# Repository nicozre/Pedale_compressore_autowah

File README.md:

# Pedale per chitarra: compressore a OTA + auto-wah

Progetto open source di un pedale per chitarra analogico che combina in un'unica scheda un **compressore** (OTA con *current stealing*) e un effetto **auto-wah** (filtro a due poli OTA-C con risonanza). Tutti i componenti sono a foro passante (THT), così da poter essere saldati a mano.

Il progetto nasce come tesi di laurea (Università degli studi di Trento, Dipartimento di ingegneria industriale: Robotica e Meccatronica, a.a. 2025/2026, autore Nicolò Ozretić, relatore Lucio Pancheri).

> ## ⚠️ Stato del progetto: NON ancora concluso
>
> - Il progetto è alla **fase di progettazione e simulazione**: il pedale **non è stato ancora costruito né misurato**.
> - I risultati riportati (guadagno, soglia, consumi, distorsione) vengono da simulazioni LTspice, non da misure.
> - Le schede **non sono state ordinate né verificate**: se le ordini, lo fai a tuo rischio.
> - È nota almeno una modifica da introdurre al prototipo: un **resistore di shunt (circa 680 Ω)** tra l'ingresso invertente dell'OTA del VCA e V<sub>bias</sub>, che realizza nel circuito reale l'attenuazione d'ingresso assunta nelle simulazioni. Non è ancora nello schema KiCad (vedi la tesi, Capitolo 5 e Conclusioni).
> - Questo repository verrà aggiornato man mano che il lavoro prosegue. Controlla la sezione *Cronologia* per le novità.

## Caratteristiche (da simulazione)

| | |
|---|---|
| Alimentazione | solo alimentatore da muro a 9 V (nessuna batteria) |
| Consumo | 19–23 mA senza LED, 26–30 mA con LED (233–271 mW) |
| Compressore | guadagno ≈ 10 dB sotto soglia, soglia ≈ 250 mV, rapporto ≈ 2,6:1, attacco ≈ 4 ms, rilascio ≈ 200 ms |
| Auto-wah | picco di risonanza ≈ 13 dB (Q ≈ 4,5), frequenza di picco da ≈ 235 Hz a ≈ 2,6 kHz, comandata dall'inviluppo |
| Componenti attivi | 2 × LM13700, 2 × TL074, TLE2426 (massa virtuale 4,5 V) |
| Controlli | SUSTAIN, DECAY, SENS, MASTER, trimmer di livello |
| Footswitch | 3PDT (serie FS5700) |

## Contenuto del repository

```
hardware/   progetto KiCad (schema, circuito stampato, librerie)
produzione/ file Gerber, distinta componenti (BOM) e posizioni, per ordinare la scheda
simulazioni/ file LTspice e script
tesi/       sorgenti LaTeX e PDF della tesi
docs/       tutorial (acquisto, montaggio, prove)
```

*(La struttura potrà cambiare: i file si aggiungeranno man mano.)*

## Tutorial: ordinare e costruire il pedale

> Il tutorial completo sarà pubblicato qui in `docs/` quando il progetto sarà verificato su un prototipo. Questa è la traccia di ciò che conterrà.

1. **Strumenti necessari**: saldatore a stagno, stagno, tronchesine, multimetro, cacciaviti, alimentatore da muro a 9 V (centro negativo, come la maggior parte dei pedali), cavi jack.
2. **Ordinare il circuito stampato**: caricare i file Gerber della cartella `produzione/` su un servizio di produzione di PCB (JLCPCB, PCBWay o simili) e scegliere le opzioni indicate nel tutorial (spessore, finitura, numero di strati).
3. **Ordinare i componenti**: dalla distinta componenti (BOM) in `produzione/`, presso un distributore di componenti elettronici (Mouser, Farnell, Digi-Key, RS o simili). Il tutorial indicherà le alternative equivalenti per i componenti più difficili da reperire.
4. **Montaggio**: ordine di saldatura consigliato (resistori, diodi, zoccoli per i circuiti integrati, condensatori, transistor, componenti ingombranti, potenziometri, connettori, footswitch), con attenzione alla polarità dei condensatori elettrolitici, dei diodi e dei circuiti integrati.
5. **Prima accensione e prove**: controllo della tensione di alimentazione e di V<sub>bias</sub> (4,5 V) prima di inserire i circuiti integrati, verifica dei consumi, prova con una chitarra e regolazione del trimmer.
6. **Contenitore**: forature, montaggio dei controlli e del footswitch.

### Preventivo indicativo

Un preventivo del costo di scheda e componenti **non è ancora disponibile**: verrà aggiunto qui quando saranno disponibili i prezzi di un fornitore di PCB e di un distributore di componenti (con la data di consultazione).

## Sorgenti della tesi

La cartella `tesi/` contiene il progetto LaTeX (compilabile con `pdflatex`, ad esempio su Overleaf) e il PDF.

## Licenza

*Da definire.* Per un progetto di hardware aperto si prevede una licenza CERN-OHL per i file di progetto e una licenza Creative Commons (CC BY) per la documentazione. Fino a quando non sarà aggiunto un file `LICENSE`, valgono i diritti d'autore dell'autore.

## Cronologia

- **novembre 2026**: prima pubblicazione del repository (progetto in fase di progettazione e simulazione).

## Contatti e contributi

Per segnalazioni, errori o miglioramenti apri una *Issue* in questo repository. I contributi sono benvenuti, in particolare le misure sul prototipo, se lo costruisci.

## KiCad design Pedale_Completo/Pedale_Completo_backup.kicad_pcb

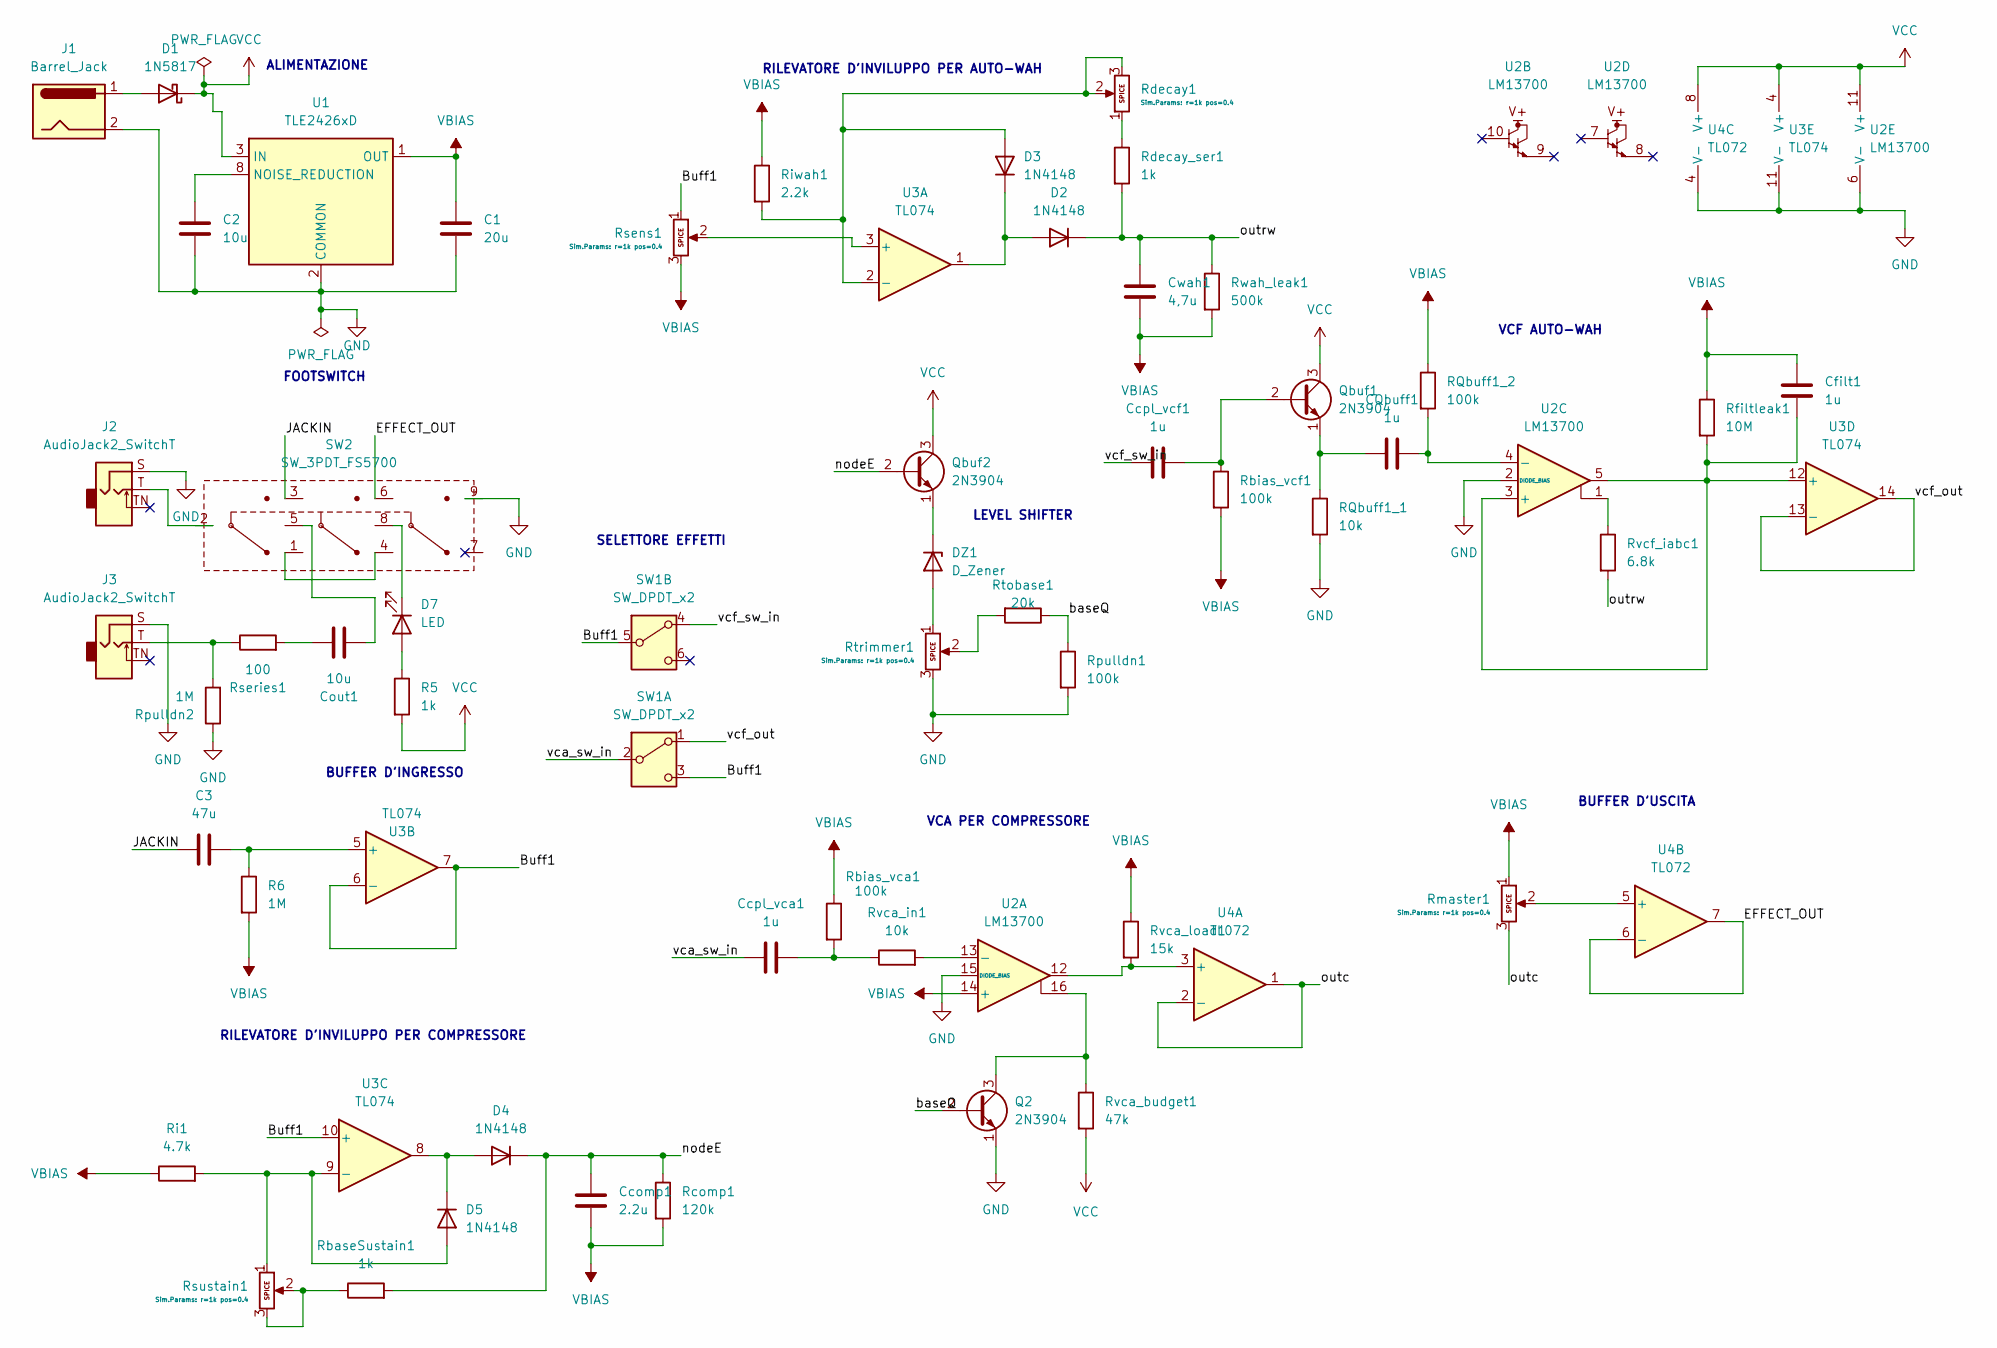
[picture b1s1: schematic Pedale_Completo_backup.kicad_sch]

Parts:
C1: 20u; CP_Radial_D5.0mm_P2.00mm
C2: 10u; CP_Radial_D5.0mm_P2.00mm
C3: 47u; CP_Radial_D6.3mm_P2.50mm
CQbuff1: 1u; CP_Radial_D5.0mm_P2.00mm
Ccomp1: 2.2u; CP_Radial_D5.0mm_P2.00mm
Ccpl_vca1: 1u; CP_Radial_D5.0mm_P2.00mm
Ccpl_vcf1: 1u; CP_Radial_D5.0mm_P2.00mm
Cfilt1: 1u; C_Disc_D5.0mm_W2.5mm_P5.00mm
Cout1: 10u; CP_Radial_D5.0mm_P2.00mm
Cwah1: 4,7u; CP_Radial_D5.0mm_P2.00mm
D1: 1N5817; D_DO-41_SOD81_P10.16mm_Horizontal
D2, D3, D4, D5: 1N4148; D_DO-35_SOD27_P7.62mm_Horizontal
D7: LED; LED_D5.0mm
DZ1: D_Zener; D_DO-35_SOD27_P7.62mm_Horizontal
J1: Barrel_Jack; BarrelJack_CUI_PJ-102AH_Horizontal
J2, J3: AudioJack2_SwitchT; Jack_Mono_SwitchedT_PCB_ACJM
Q2: 2N3904; TO-92_Inline
Qbuf1, Qbuf2: 2N3904; TO-92_Inline
R5: 1k; R_Axial_DIN0207_L6.3mm_D2.5mm_P10.16mm_Horizontal
R6: 1M; R_Axial_DIN0207_L6.3mm_D2.5mm_P10.16mm_Horizontal
RQbuff1_1: 10k; R_Axial_DIN0207_L6.3mm_D2.5mm_P10.16mm_Horizontal
RQbuff1_2: 100k; R_Axial_DIN0207_L6.3mm_D2.5mm_P10.16mm_Horizontal
RbaseSustain1: 1k; R_Axial_DIN0207_L6.3mm_D2.5mm_P10.16mm_Horizontal
Rbias_vca1: 100k; R_Axial_DIN0207_L6.3mm_D2.5mm_P10.16mm_Horizontal
Rbias_vcf1: 100k; R_Axial_DIN0207_L6.3mm_D2.5mm_P10.16mm_Horizontal
Rcomp1: 120k; R_Axial_DIN0207_L6.3mm_D2.5mm_P10.16mm_Horizontal
Rdecay1: Potentiometer; Potentiometer_Alps_RK09K_Single_Vertical
Rdecay_ser1: 1k; R_Axial_DIN0207_L6.3mm_D2.5mm_P10.16mm_Horizontal
Rfiltleak1: 10M; R_Axial_DIN0207_L6.3mm_D2.5mm_P10.16mm_Horizontal
Ri1: 4.7k; R_Axial_DIN0207_L6.3mm_D2.5mm_P10.16mm_Horizontal
Riwah1: 2.2k; R_Axial_DIN0207_L6.3mm_D2.5mm_P10.16mm_Horizontal
Rmaster1: Potentiometer; Potentiometer_Alps_RK09K_Single_Vertical
Rpulldn1: 100k; R_Axial_DIN0207_L6.3mm_D2.5mm_P10.16mm_Horizontal
Rpulldn2: 1M; R_Axial_DIN0207_L6.3mm_D2.5mm_P10.16mm_Horizontal
Rsens1: Potentiometer; Potentiometer_Alps_RK09K_Single_Vertical
Rseries1: 100; R_Axial_DIN0207_L6.3mm_D2.5mm_P10.16mm_Horizontal
Rsustain1: Potentiometer; Potentiometer_Alps_RK09K_Single_Vertical
Rtobase1: 20k; R_Axial_DIN0207_L6.3mm_D2.5mm_P10.16mm_Horizontal
Rtrimmer1: Potentiometer; Potentiometer_Bourns_3296W_Vertical
Rvca_budget1: 47k; R_Axial_DIN0207_L6.3mm_D2.5mm_P10.16mm_Horizontal
Rvca_in1: 10k; R_Axial_DIN0207_L6.3mm_D2.5mm_P10.16mm_Horizontal
Rvca_load1: 15k; R_Axial_DIN0207_L6.3mm_D2.5mm_P10.16mm_Horizontal
Rvcf_iabc1: 6.8k; R_Axial_DIN0207_L6.3mm_D2.5mm_P10.16mm_Horizontal
Rwah_leak1: 500k; R_Axial_DIN0207_L6.3mm_D2.5mm_P10.16mm_Horizontal
SW1: SW_DPDT_x2; SW_NKK_GW12LJP
SW2: SW_3PDT_FS5700
U1: TLE2426xD; DIP-8_W7.62mm
U2: LM13700; DIP-16_W7.62mm
U3: TL074; DIP-14_W7.62mm
U4: TL072; DIP-8_W7.62mm

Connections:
/Buff1: Rsens1.1, SW1.3 (C), SW1.5 (B), U3.6 (-), U3.7, U3.10 (+)
/EFFECT_OUT: SW2.6, U4.6 (-), U4.7
/JACKIN: C3.2, SW2.3
/baseQ: Q2.2 (B), Rpulldn1.1, Rtobase1.1
/nodeE: Ccomp1.1, D4.1 (K), Qbuf2.2 (B), RbaseSustain1.2, Rcomp1.1
/outc: Rmaster1.3, U4.1, U4.2 (-)
/outrw: Cwah1.1, D2.1 (K), Rdecay_ser1.2, Rvcf_iabc1.2, Rwah_leak1.1
/vca_sw_in: Ccpl_vca1.1, SW1.2 (B)
/vcf_out: SW1.1 (A), U3.13 (-), U3.14
/vcf_sw_in: Ccpl_vcf1.1, SW1.4 (A)
GND: C1.2, C2.2, J1.2, J2.S, J3.S, Q2.1 (E), RQbuff1_1.2, Rpulldn1.2, Rpulldn2.1, Rtrimmer1.3, SW2.9, U1.2 (COMMON), U2.2 (DIODE_BIAS), U2.6 (V-), U2.15 (DIODE_BIAS), U3.11 (V-), U4.4 (V-)
unnamed: Ccpl_vca1.2, Rbias_vca1.2, Rvca_in1.1
unnamed: Cout1.1, SW2.5
unnamed: Cout1.2, Rseries1.2
unnamed: D1.2 (A), J1.1
unnamed: D2.2 (A), D3.1 (K), U3.1
unnamed: D3.2 (A), Rdecay1.2, Rdecay1.3, Riwah1.2, U3.2 (-)
unnamed: D4.2 (A), D5.1 (K), U3.8
unnamed: D5.2 (A), Ri1.2, Rsustain1.1, U3.9 (-)
unnamed: D7.2 (A), R5.1
unnamed: D7.1 (K), SW2.8
unnamed: DZ1.2 (A), Rtrimmer1.1
unnamed: DZ1.1 (K), Qbuf2.1 (E)
unnamed: J2.T, SW2.2
unnamed: J3.T, Rpulldn2.2, Rseries1.1
unnamed: Q2.3 (C), Rvca_budget1.1, U2.16
unnamed: Ccpl_vcf1.2, Qbuf1.2 (B), Rbias_vcf1.1
unnamed: CQbuff1.1, Qbuf1.1 (E), RQbuff1_1.1
unnamed: RbaseSustain1.1, Rsustain1.2, Rsustain1.3
unnamed: Rdecay1.1, Rdecay_ser1.1
unnamed: Rtobase1.2, Rtrimmer1.2
unnamed: Rvcf_iabc1.1, U2.1
unnamed: SW2.1, SW2.4
unnamed: C2.1, U1.8 (NOISE_REDUCTION)
unnamed: Rvca_in1.2, U2.13 (-)
unnamed: Cfilt1.2, Rfiltleak1.2, U2.3 (+), U2.5, U3.12 (+)
unnamed: CQbuff1.2, RQbuff1_2.2, U2.4 (-)
unnamed: Rsens1.2, U3.3 (+)
unnamed: C3.1, R6.1, U3.5 (+)
unnamed: Rvca_load1.2, U2.12, U4.3 (+)
unnamed: Rmaster1.2, U4.5 (+)
VBIAS: C1.1, Ccomp1.2, Cfilt1.1, Cwah1.2, R6.2, RQbuff1_2.1, Rbias_vca1.1, Rbias_vcf1.2, Rcomp1.2, Rfiltleak1.1, Ri1.1, Riwah1.1, Rmaster1.1, Rsens1.3, Rvca_load1.1, Rwah_leak1.2, U1.1 (OUT), U2.14 (+)
VCC: D1.1 (K), Qbuf1.3 (C), Qbuf2.3 (C), R5.2, Rvca_budget1.2, U1.3 (IN), U2.11 (V+), U3.4 (V+), U4.8 (V+)

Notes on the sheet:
RILEVATORE D'INVILUPPO PER COMPRESSORE
BUFFER D'USCITA
BUFFER D'INGRESSO
RILEVATORE D'INVILUPPO PER AUTO-WAH
SELETTORE EFFETTI
VCA PER COMPRESSORE
FOOTSWITCH
VCF AUTO-WAH
LEVEL SHIFTER
ALIMENTAZIONE

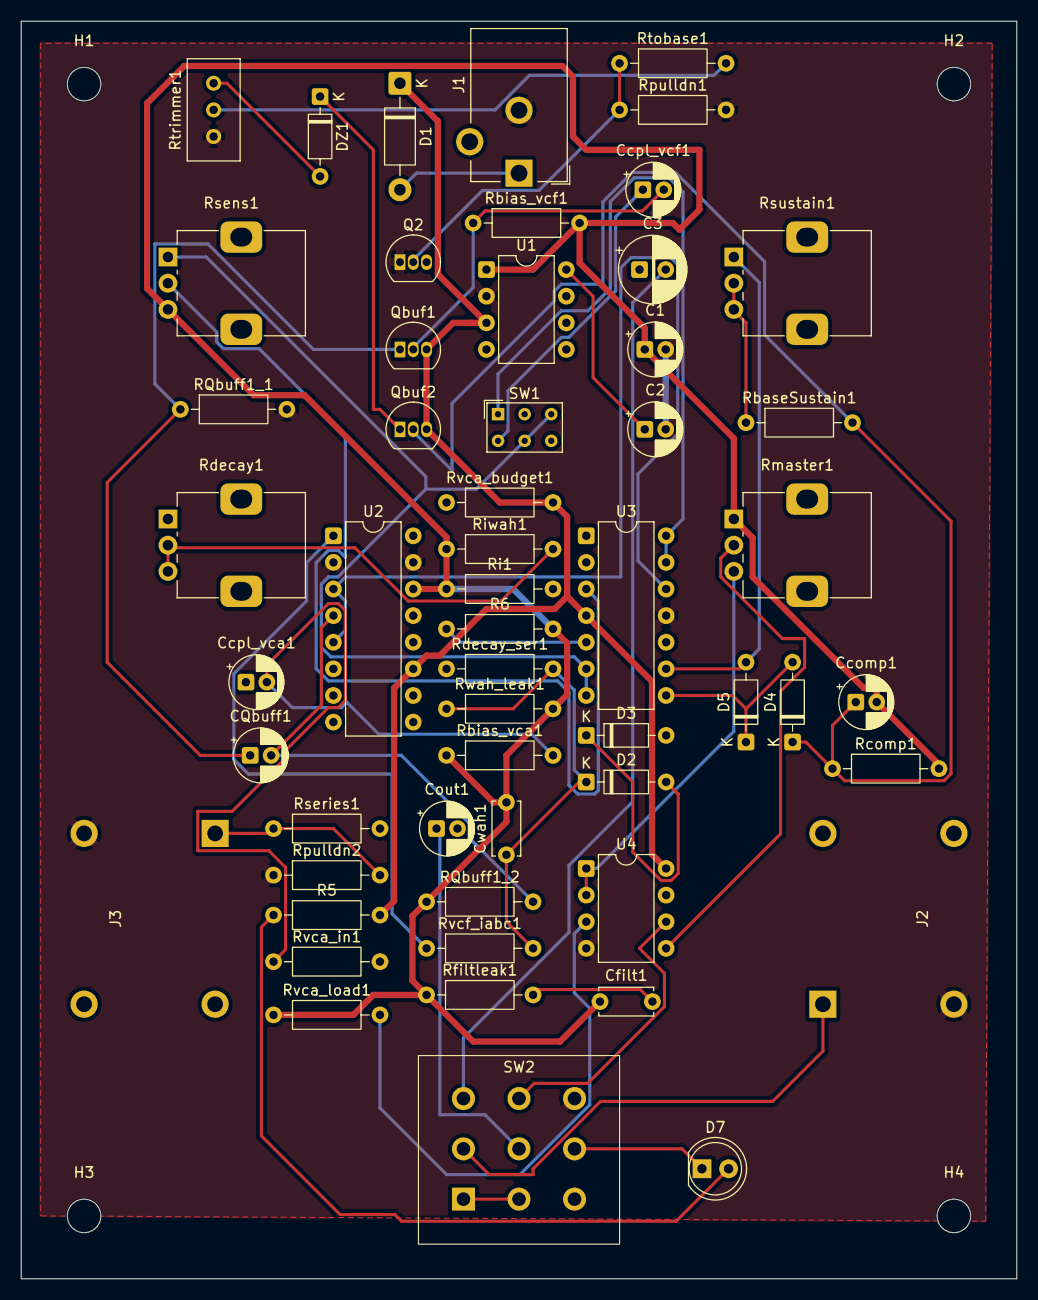
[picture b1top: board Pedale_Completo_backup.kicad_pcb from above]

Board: 2 copper layers, 95.0 x 120.0 mm, 59 parts (0 on the bottom side), 43 nets.

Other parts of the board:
H1, H2, H3, H4: MountingHole_3.2mm_M3
